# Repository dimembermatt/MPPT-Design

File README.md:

# :sunny: Sunscatter MPPT-Design - Gen 2 Maximum Power Point Tracker Board

Design and documentation of a custom MPPT for LHR Solar. Created in part with
Professor Alex Hanson's ECE 394J Power Electronics Class.

---

## Repository Structure

- **datasheets** - contains datasheets for major components of the Sunscatter.
- **docs** - contains documentation on how to build, test, and use the Sunscatter.
- **fw** - contains fw that is loaded onto the Sunscatter.
  - **tests** - test programs used to characterize and validate the Sunscatter.
  - **src** - main program used to run the Sunscatter.
  - **inc** - internally developed libraries specific for the Sunscatter.
  - **lib** - third party libraries used by the Sunscatter.
- **hw**
  - **footprints** - project specfic footprint association files for the Sunscatter.
  - **models** - 3d .step files for the PCB 3d viewer.
  - **symbols** - project specific symbol files for the Sunscatter.
  - **vX_Y_Z** - frozen versioning folder for PCB production files.
  - design files
- **sim** - contains a KiCAD project of the bare DC-DC converter of the MPPT, using SPICE parts for simulation.
- **sw** - contains relevant software for operating the automated design pipeline.
  - **design_files**
  - **design_procedures**

---

## Maintainers

The current maintainer of this project is Matthew Yu as of 07/17/2023. His email
is [matthewjkyu@gmail.com](matthewjkyu@gmail.com).

Contributors to the HW and FW encompass many dedicated students, including:

- Jacob Pustilnik
- Pranav Rama
- Sharon Chen

Special thanks to Professor Gary Hallock, who supervised the development and
design of this project.

---

## Versioning

This PCB is on unified version `0.2.0`. Every time the schematic and/or layout
is updated, this version number should go up. We use [semantic
versioning](https://semver.org/) to denote between versions. See the
[changelog](./docs/CHANGELOG.md) for more details.

---

## TODO

### Documentation

### HW

### FW

### SW

### Sim

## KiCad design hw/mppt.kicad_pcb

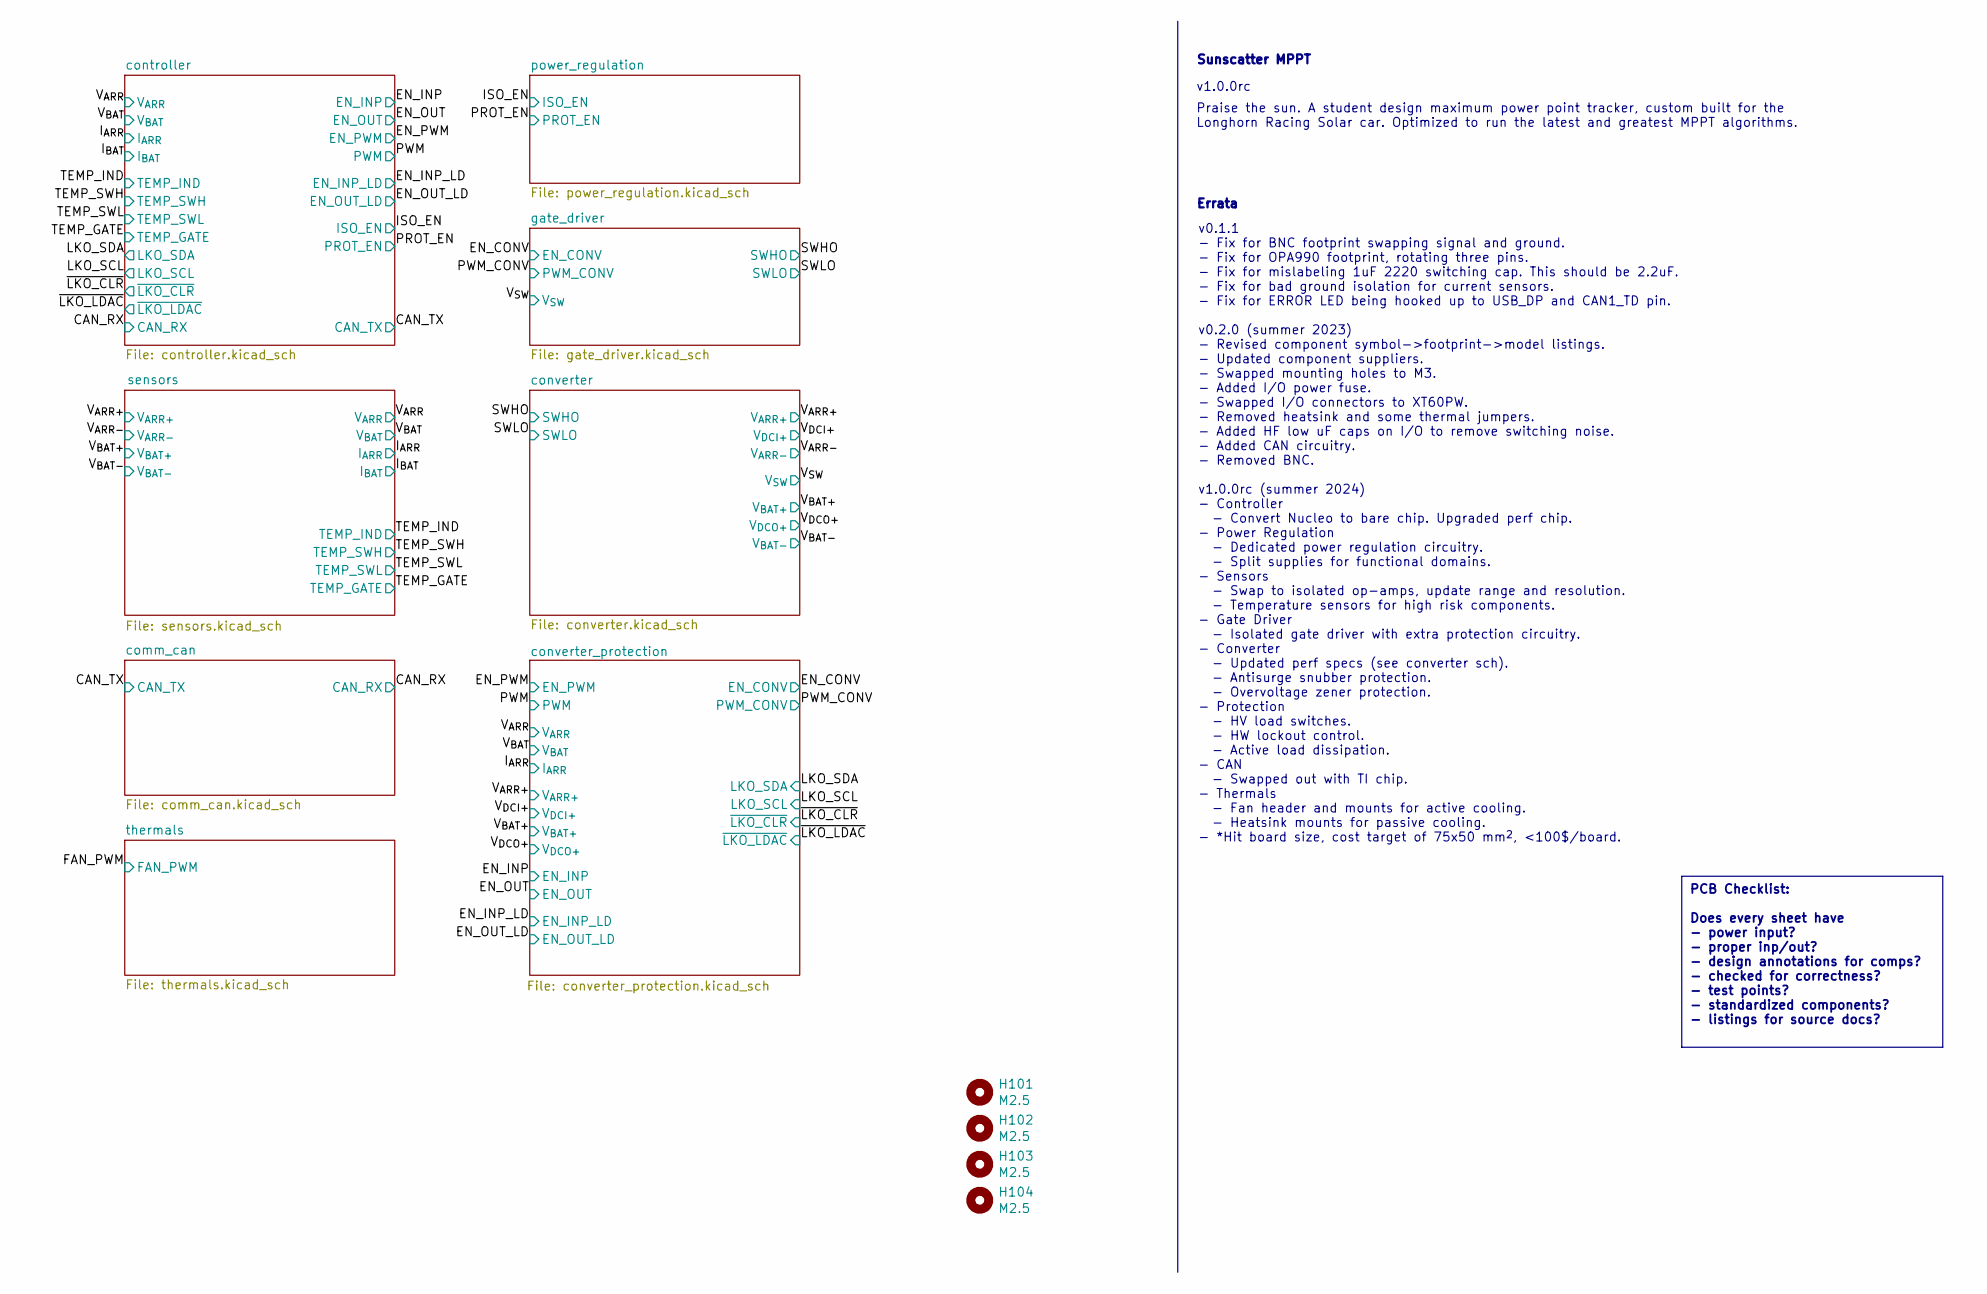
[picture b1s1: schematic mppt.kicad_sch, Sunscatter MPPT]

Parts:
H101, H102, H103, H104: M2.5; MountingHole_2.5mm

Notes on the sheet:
PCB Checklist: Does every sheet have - power input? - proper inp/out? - design annotations for comps? - checked for correctness? - test points? - standardized components? - listings for source docs?
Praise the sun. A student design maximum power point tracker, custom built for the Longhorn Racing Solar car. Optimized to run the latest and greatest MPPT algorithms.
Sunscatter MPPT
v1.0.0rc
Errata
v0.1.1 - Fix for BNC footprint swapping signal and ground. - Fix for OPA990 footprint, rotating three pins. - Fix for mislabeling 1uF 2220 switching cap. This should be 2.2uF. - Fix for bad ground isolation for current sensors. - Fix for ERROR LED being hooked up to USB_DP and CAN1_TD pin. v0.2.0 (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

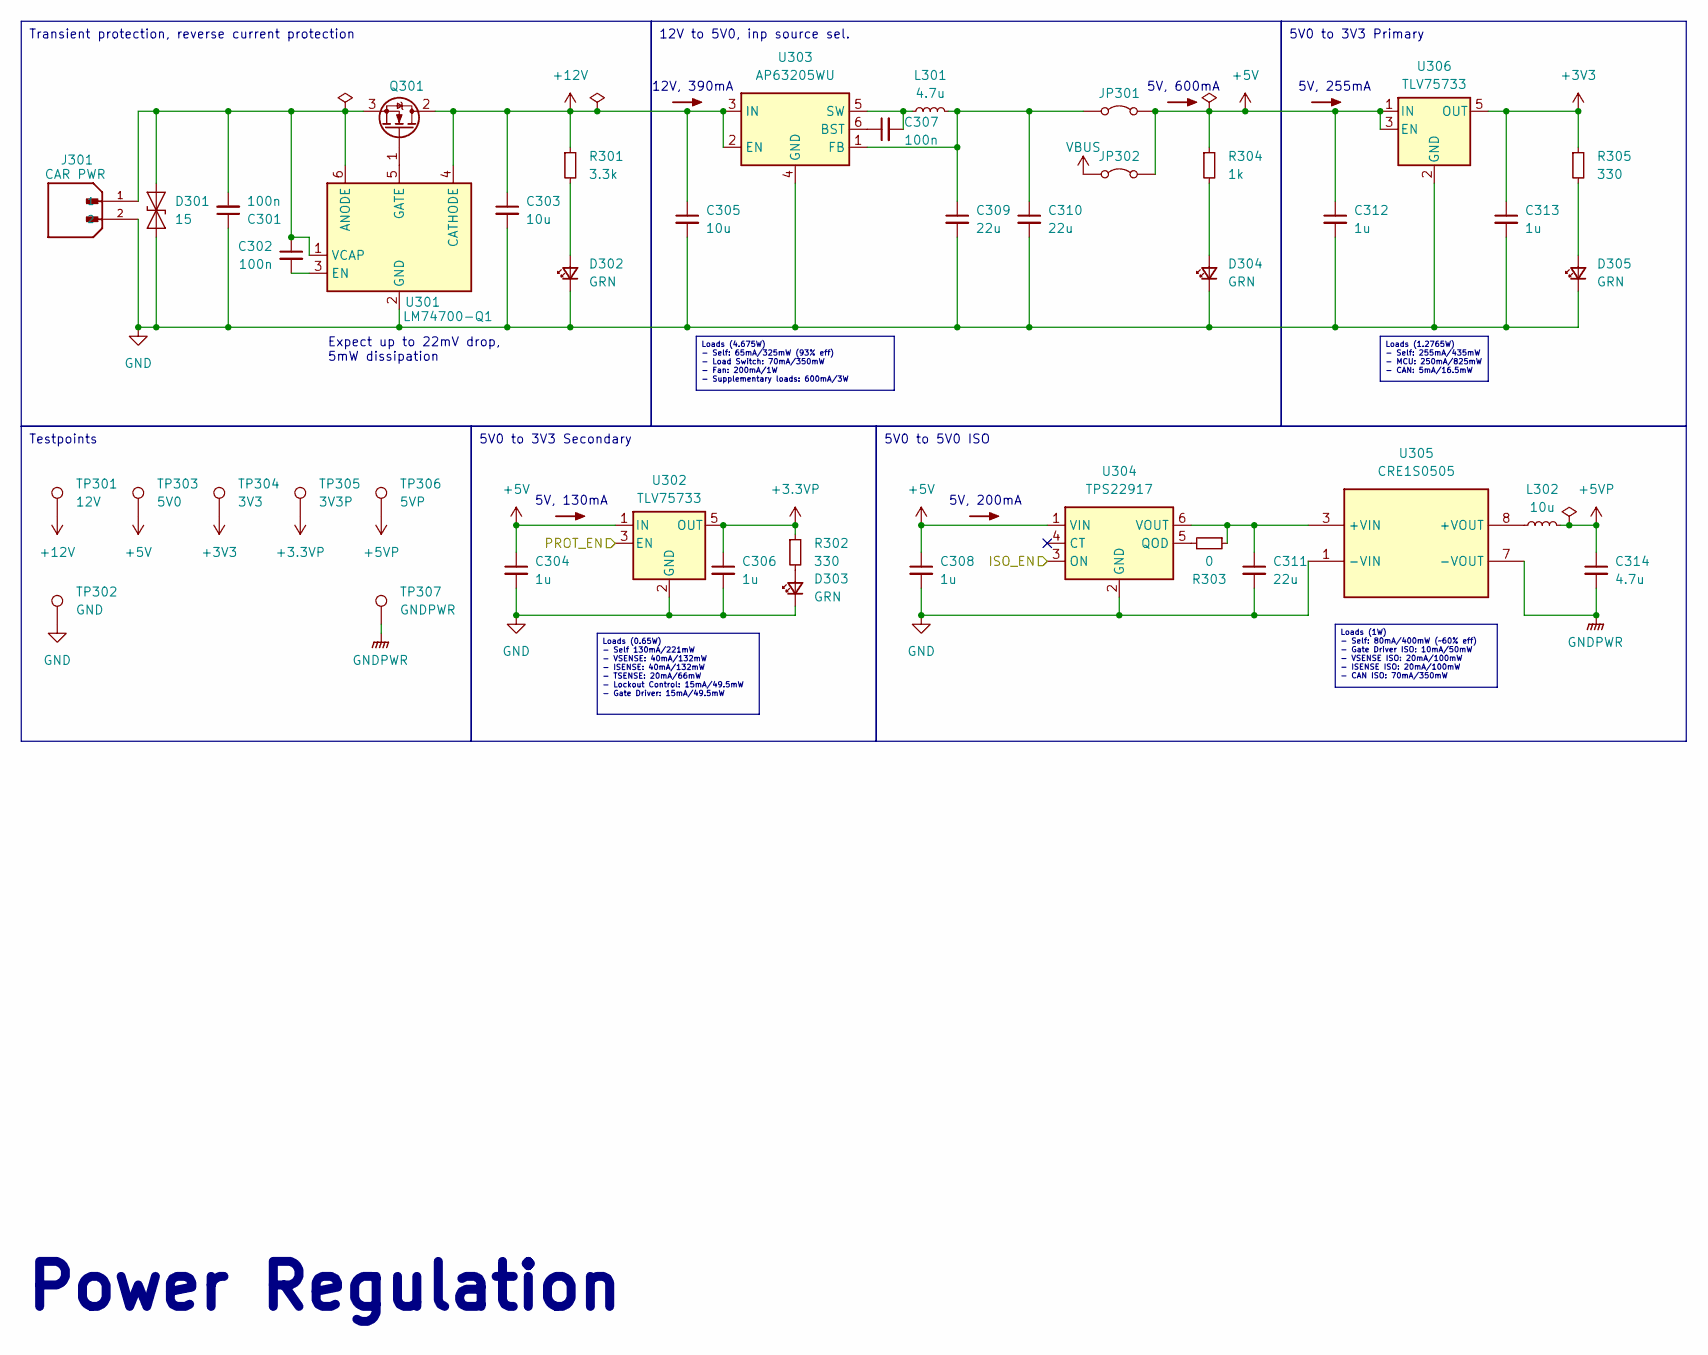
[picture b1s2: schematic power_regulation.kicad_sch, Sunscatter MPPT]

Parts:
C301, C302, C307: 100n; R_0402_1005Metric; LCSC Part # C307331
C303, C305: 10u; R_0805_2012Metric
C304, C306, C308, C312, C313: 1u; R_0402_1005Metric; LCSC Part # C307454
C309, C310, C311: 22u; R_0805_2012Metric
C314: 4.7u; R_0402_1005Metric; LCSC Part # C318563
D301: 15; D_SMA
D302, D303, D304, D305: GRN; LED_0402_1005Metric
J301: CAR PWR; molex_microfit_43650_0227
JP301, JP302: Jumper_2_Bridged; PinHeader_1x02_P2.54mm_Vertical
L301: 4.7u; L_TDK_VLS6045EX_VLS6045AF
L302: 10u; L_TDK_VLS6045EX_VLS6045AF
Q301: Q_NMOS_GDS; SOT-223-3_TabPin2
R301: 3.3k; R_0402_1005Metric; LCSC Part # C25890
R302, R305: 330; R_0402_1005Metric; LCSC Part # C25105
R303: 0; R_0402_1005Metric
R304: 1k; R_0402_1005Metric; LCSC Part # C11702
TP301: 12V; TestPoint_Pad_D1.5mm
TP302: GND; TestPoint_Pad_D1.5mm
TP303: 5V0; TestPoint_Pad_D1.5mm
TP304: 3V3; TestPoint_Pad_D1.5mm
TP305: 3V3P; TestPoint_Pad_D1.5mm
TP306: 5VP; TestPoint_Pad_D1.5mm
TP307: GNDPWR; TestPoint_Pad_D1.5mm
U301: LM74700-Q1; SOT-23-6
U302, U306: TLV75733; SOT-23-5
U303: AP63205WU; TSOT-23-6
U304: TPS22917; SOT-23-6
U305: CRE1S0505; murata_CRE1S0505_MEC

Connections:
+3.3VP: C306.1, R302.1, TP305.1, U302.5 (OUT); also elsewhere on the board
+3V3: C313.1, R305.1, TP304.1, U306.5 (OUT); also elsewhere on the board
+5V: C304.1, C308.1, C312.1, JP301.2 (B), JP302.2 (B), R304.1, TP303.1, U302.1 (IN), U304.1 (VIN), U306.1 (IN), U306.3 (EN); also elsewhere on the board
+5VP: C314.1, L302.2, TP306.1; also elsewhere on the board
+12V: C303.1, C305.1, Q301.2 (D), R301.1, TP301.1, U301.4 (CATHODE), U303.2 (EN), U303.3 (IN)
/ISO_EN: U304.3 (ON); also elsewhere on the board
/PROT_EN: U302.3 (EN); also elsewhere on the board
GND: C301.1, C303.2, C304.2, C305.2, C306.2, C308.2, C309.2, C310.2, C311.2, C312.2, C313.2, D301.1 (A1), D302.1 (K), D303.1 (K), D304.1 (K), D305.1 (K), J301.2, TP302.1, U301.2 (GND), U302.2 (GND), U303.4 (GND), U304.2 (GND), U305.1 (-VIN), U306.2 (GND); also elsewhere on the board
GNDPWR: C314.2, TP307.1, U305.7 (-VOUT); also elsewhere on the board
unnamed: C301.2, C302.1, D301.2 (A2), J301.1, Q301.3 (S), U301.1 (VCAP), U301.6 (ANODE)
unnamed: D302.2 (A), R301.2
unnamed: D303.2 (A), R302.2
unnamed: D304.2 (A), R304.2
unnamed: D305.2 (A), R305.2
unnamed: C309.1, C310.1, JP301.1 (A), L301.2, U303.1 (FB)
unnamed: Q301.1 (G), U301.5 (GATE)
unnamed: C302.2, U301.3 (EN)
unnamed: C307.1, U303.6 (BST)
unnamed: C307.2, L301.1, U303.5 (SW)
unnamed: R303.2, U304.5 (QOD)
unnamed: C311.1, R303.1, U304.6 (VOUT), U305.3 (+VIN)
unnamed: L302.1, U305.8 (+VOUT)
VBUS: JP302.1 (A); also elsewhere on the board

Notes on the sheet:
Testpoints
Loads (1W) - Self: 80mA/400mW (~60% eff) - Gate Driver ISO: 10mA/50mW - VSENSE ISO: 20mA/100mW - ISENSE ISO: 20mA/100mW - CAN ISO: 70mA/350mW
Transient protection, reverse current protection
5V0 to 3V3 Primary
5V0 to 5V0 ISO
Loads (4.675W) - Self: 65mA/325mW (93% eff) - Load Switch: 70mA/350mW - Fan: 200mA/1W - Supplementary loads: 600mA/3W
Loads (0.65W) - Self 130mA/221mW - VSENSE: 40mA/132mW - ISENSE: 40mA/132mW - TSENSE: 20mA/66mW - Lockout Control: 15mA/49.5mW - Gate Driver: 15mA/49.5mW
5V0 to 3V3 Secondary
12V to 5V0, inp source sel.
Loads (1.2765W) - Self: 255mA/435mW - MCU: 250mA/825mW - CAN: 5mA/16.5mW
Power Regulation
5V, 200mA
5V, 255mA
12V, 390mA
5V, 600mA
5V, 130mA
Expect up to 22mV drop, 5mW dissipation

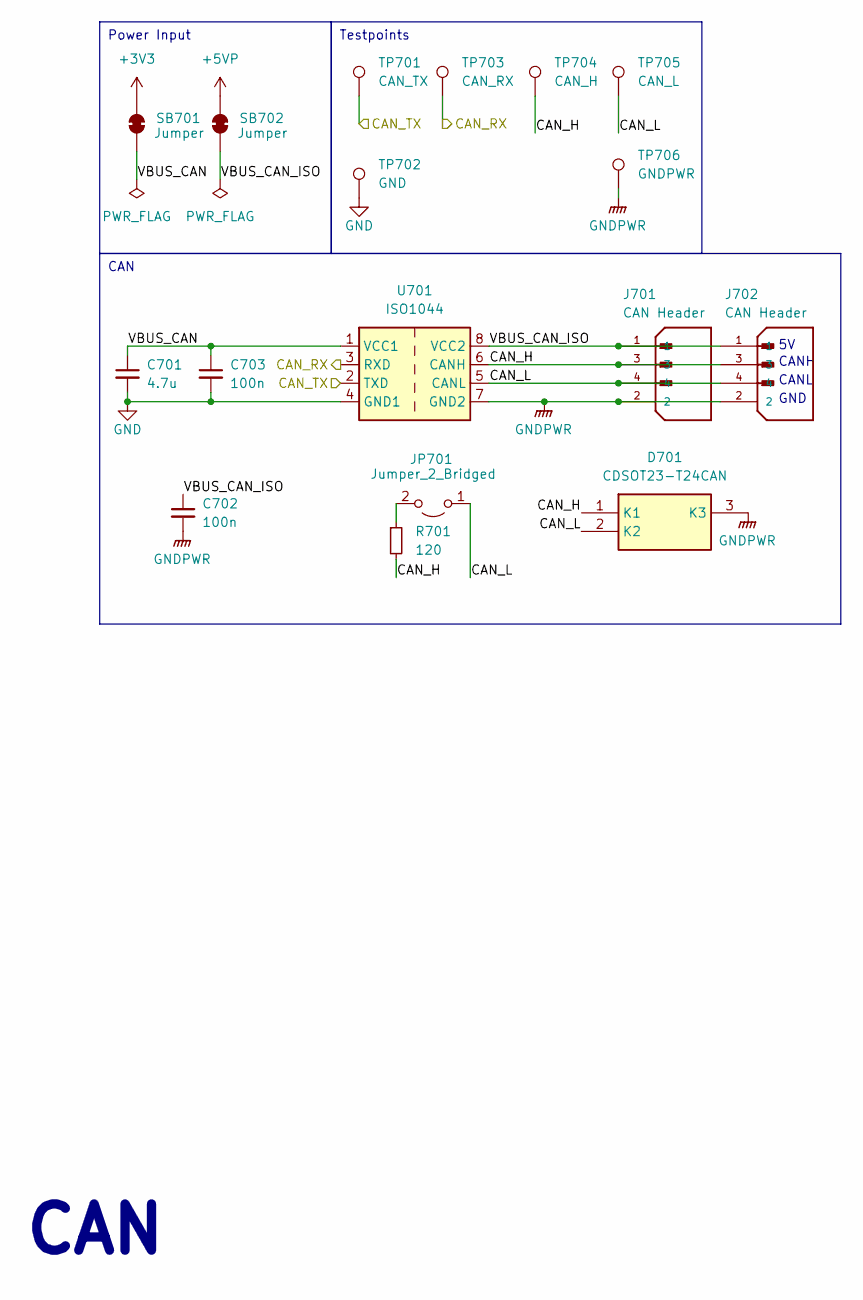
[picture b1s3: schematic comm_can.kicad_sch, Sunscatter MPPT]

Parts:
C701: 4.7u; R_0402_1005Metric; LCSC Part # C318563
C702, C703: 100n; R_0402_1005Metric; LCSC Part # C307331
D701: CDSOT23-T24CAN; bourns_CDSOT23_T24CAN
J701, J702: CAN Header; molex_microfit_43650_0427
JP701: Jumper_2_Bridged; PinHeader_1x02_P2.54mm_Vertical
R701: 120; R_0402_1005Metric; LCSC Part # C25079
SB701, SB702: Jumper; SolderJumper-2_P1.3mm_Open_TrianglePad1.0x1.5mm
TP701: CAN_TX; TestPoint_Pad_D1.5mm
TP702: GND; TestPoint_Pad_D1.5mm
TP703: CAN_RX; TestPoint_Pad_D1.5mm
TP704: CAN_H; TestPoint_Pad_D1.5mm
TP705: CAN_L; TestPoint_Pad_D1.5mm
TP706: GNDPWR; TestPoint_Pad_D1.5mm
U701: ISO1044; SOIC-8_3.9x4.9mm_P1.27mm

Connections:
+3V3: SB701.1 (A); also elsewhere on the board
+5VP: SB702.1 (A); also elsewhere on the board
/CAN_RX: TP703.1, U701.3 (RXD); also elsewhere on the board
/CAN_TX: TP701.1, U701.2 (TXD); also elsewhere on the board
/comm_can/CAN_H: D701.1 (K1), J701.3, J702.3, R701.2, TP704.1, U701.6 (CANH)
/comm_can/CAN_L: D701.2 (K2), J701.4, J702.4, JP701.1 (A), TP705.1, U701.5 (CANL)
/comm_can/VBUS_CAN: C701.1, C703.1, SB701.2 (B), U701.1 (VCC1)
/comm_can/VBUS_CAN_ISO: C702.1, J701.1, J702.1, SB702.2 (B), U701.8 (VCC2)
GND: C701.2, C703.2, TP702.1, U701.4 (GND1); also elsewhere on the board
GNDPWR: C702.2, D701.3 (K3), J701.2, J702.2, TP706.1, U701.7 (GND2); also elsewhere on the board
unnamed: JP701.2 (B), R701.1

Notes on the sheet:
CAN
Power Input
Testpoints
CANH
GND
CANL

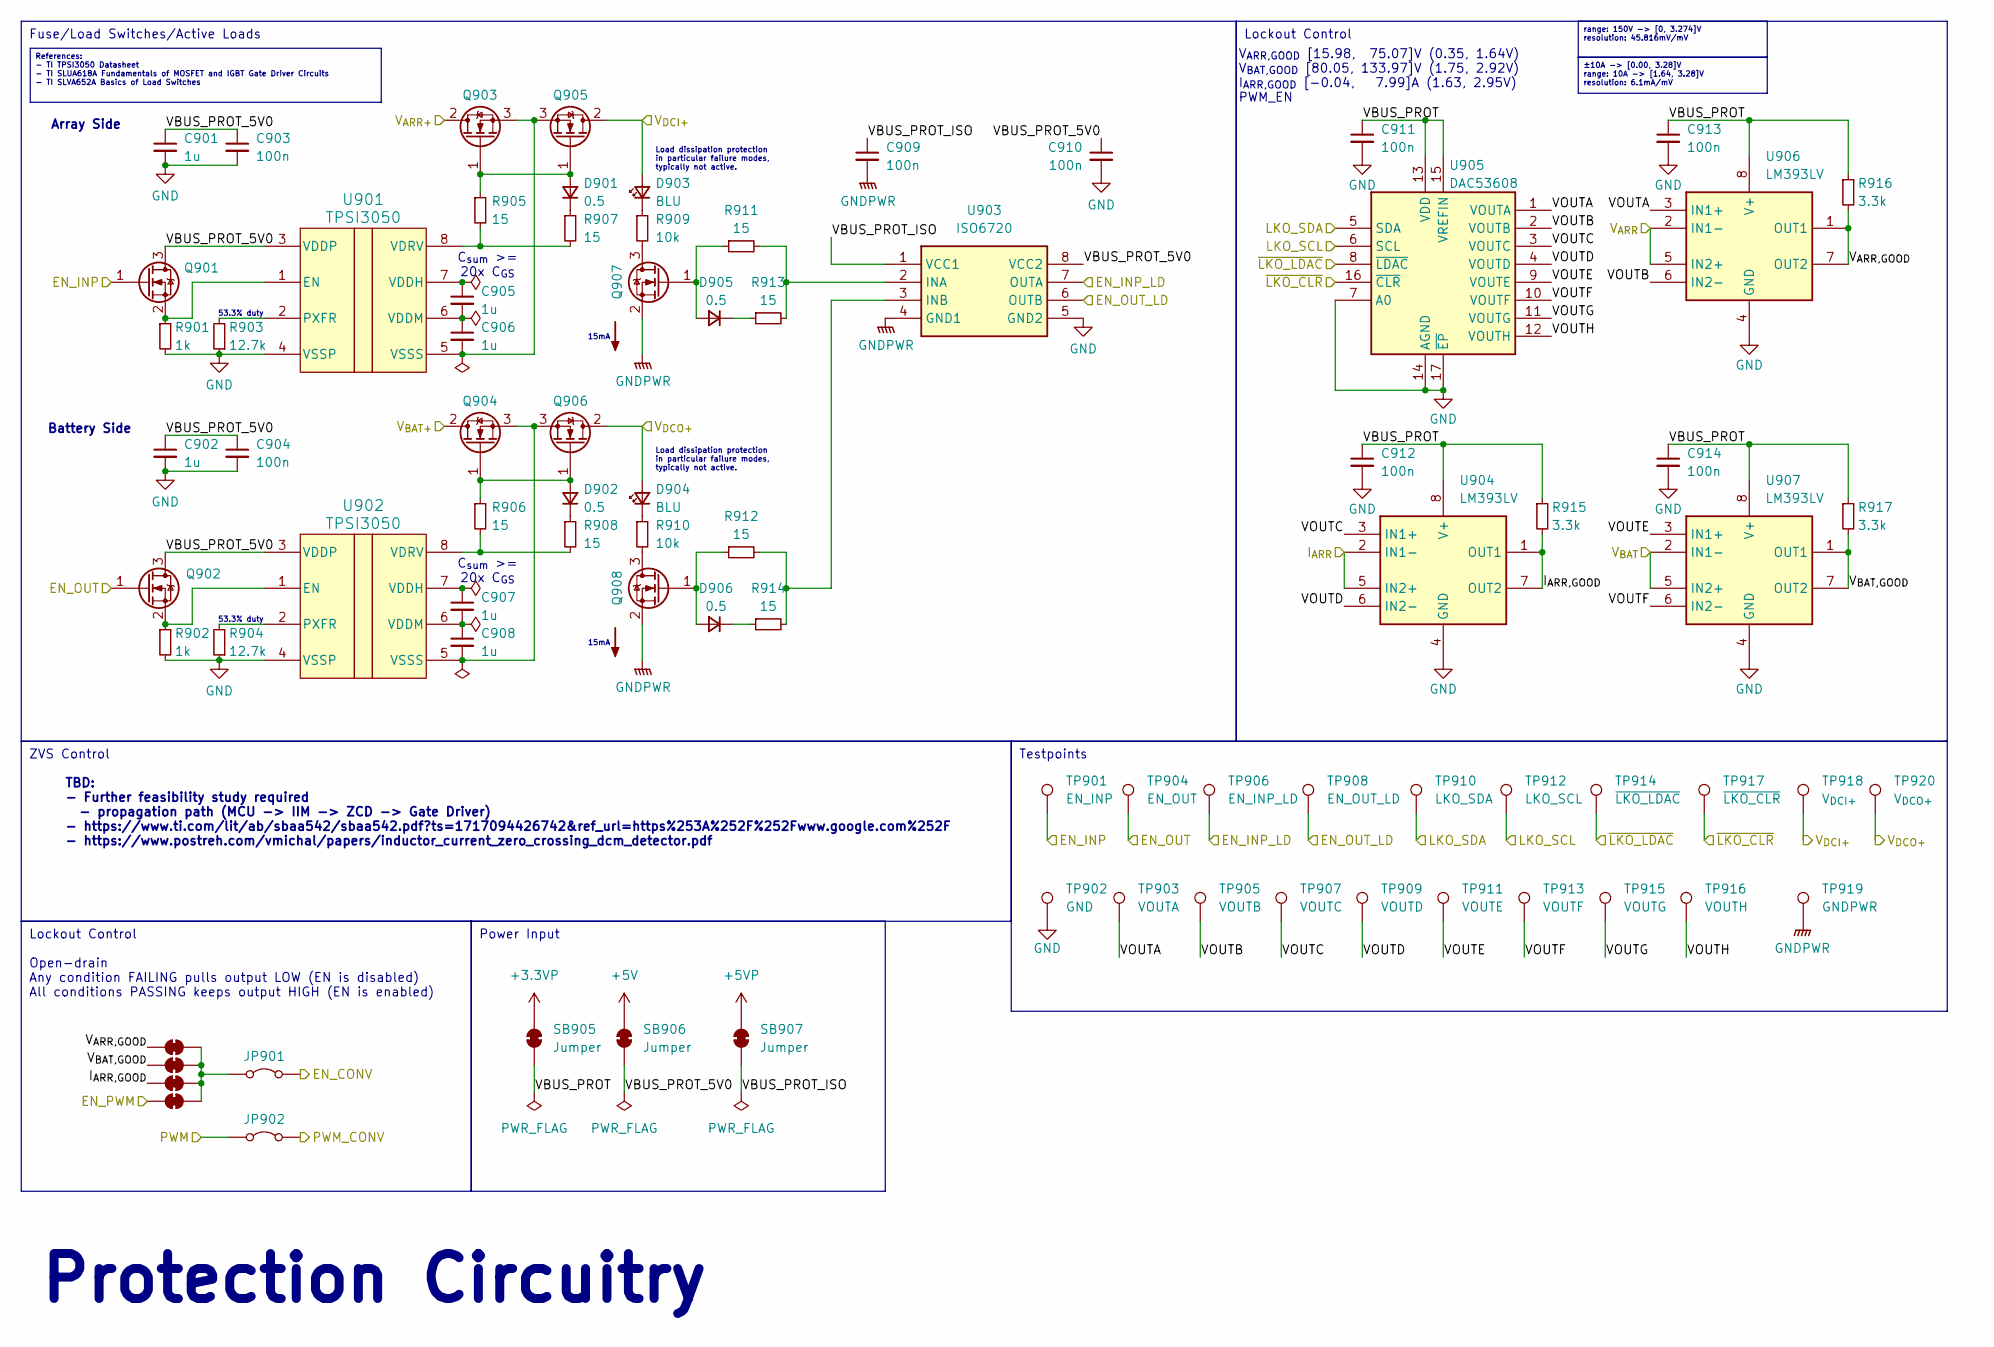
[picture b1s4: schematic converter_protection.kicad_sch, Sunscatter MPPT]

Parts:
C901, C902, C905, C906, C907, C908: 1u; R_0402_1005Metric; LCSC Part # C307454
C903, C904, C909, C910, C911, C912, C913, C914: 100n; R_0402_1005Metric; LCSC Part # C307331
D901, D902, D905, D906: 0.5; D_SMA
D903, D904: BLU; LED_0402_1005Metric
JP901, JP902: Jumper_2_Bridged; PinHeader_1x02_P2.54mm_Vertical
Q901, Q902, Q907, Q908: BSS127S; SOT-23
Q903, Q904, Q905, Q906: Q_NMOS_GDS; SOT-223-3_TabPin2
R901, R902: 1k; R_0402_1005Metric; LCSC Part # C11702
R903, R904: 12.7k; R_0402_1005Metric; LCSC Part # C25853
R905, R906, R907, R908, R911, R912, R913, R914: 15; R_0603_1608Metric; LCSC Part # C22810
R909, R910: 10k; R_2512_6332Metric_Pad1.40x3.35mm_HandSolder
R915, R916, R917: 3.3k; R_0402_1005Metric; LCSC Part # C25890
SB901, SB902, SB903, SB904, SB905, SB906, SB907: Jumper; SolderJumper-2_P1.3mm_Open_TrianglePad1.0x1.5mm
TP901: EN_INP; TestPoint_Pad_D1.5mm
TP902: GND; TestPoint_Pad_D1.5mm
TP903: VOUTA; TestPoint_Pad_D1.5mm
TP904: EN_OUT; TestPoint_Pad_D1.5mm
TP905: VOUTB; TestPoint_Pad_D1.5mm
TP906: EN_INP_LD; TestPoint_Pad_D1.5mm
TP907: VOUTC; TestPoint_Pad_D1.5mm
TP908: EN_OUT_LD; TestPoint_Pad_D1.5mm
TP909: VOUTD; TestPoint_Pad_D1.5mm
TP910: LKO_SDA; TestPoint_Pad_D1.5mm
TP911: VOUTE; TestPoint_Pad_D1.5mm
TP912: LKO_SCL; TestPoint_Pad_D1.5mm
TP913: VOUTF; TestPoint_Pad_D1.5mm
TP914: ~{LKO_LDAC}; TestPoint_Pad_D1.5mm
TP915: VOUTG; TestPoint_Pad_D1.5mm
TP916: VOUTH; TestPoint_Pad_D1.5mm
TP917: ~{LKO_CLR}; TestPoint_Pad_D1.5mm
TP918: V_{DCI+}; TestPoint_Pad_D1.5mm
TP919: GNDPWR; TestPoint_Pad_D1.5mm
TP920: V_{DCO+}; TestPoint_Pad_D1.5mm
U901, U902: TPSI3050; ti_TPS3050_DWZ
U903: ISO6720; ti_ISO6720B_DR
U904, U906, U907: LM393LV; ti_LM393LV_DR
U905: DAC53608; ti_DAC53608_RT

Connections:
+3.3VP: SB905.2 (B); also elsewhere on the board
+5V: SB906.2 (B); also elsewhere on the board
+5VP: SB907.2 (B); also elsewhere on the board
/EN_CONV: JP901.2 (B); also elsewhere on the board
/EN_INP: Q901.1 (G), TP901.1; also elsewhere on the board
/EN_INP_LD: TP906.1, U903.7 (OUTA); also elsewhere on the board
/EN_OUT: Q902.1 (G), TP904.1; also elsewhere on the board
/EN_OUT_LD: TP908.1, U903.6 (OUTB); also elsewhere on the board
/EN_PWM: SB904.1 (A); also elsewhere on the board
/I_{ARR}: U904.2 (IN1-), U904.5 (IN2+); also elsewhere on the board
/LKO_SCL: TP912.1, U905.6 (SCL); also elsewhere on the board
/LKO_SDA: TP910.1, U905.5 (SDA); also elsewhere on the board
/PWM: JP902.1 (A); also elsewhere on the board
/PWM_CONV: JP902.2 (B); also elsewhere on the board
/V_{ARR+}: Q903.2 (D); also elsewhere on the board
/V_{ARR}: U906.2 (IN1-), U906.5 (IN2+); also elsewhere on the board
/V_{BAT+}: Q904.2 (D); also elsewhere on the board
/V_{BAT}: U907.2 (IN1-), U907.5 (IN2+); also elsewhere on the board
/V_{DCI+}: D903.2 (A), Q905.2 (D), TP918.1; also elsewhere on the board
/V_{DCO+}: D904.2 (A), Q906.2 (D), TP920.1; also elsewhere on the board
/converter_protection/I_{ARR,GOOD}: R915.2, SB903.1 (A), U904.1 (OUT1), U904.7 (OUT2)
/converter_protection/VBUS_PROT: C911.1, C912.1, C913.1, C914.1, R915.1, R916.1, R917.1, SB905.1 (A), U904.8 (V+), U905.13 (VDD), U905.15 (VREFIN), U906.8 (V+), U907.8 (V+)
/converter_protection/VBUS_PROT_5V0: C901.1, C902.1, C903.1, C904.1, C910.1, Q901.3 (D), Q902.3 (D), SB906.1 (A), U901.3 (VDDP), U902.3 (VDDP), U903.8 (VCC2)
/converter_protection/VBUS_PROT_ISO: C909.1, SB907.1 (A), U903.1 (VCC1)
/converter_protection/VOUTA: TP903.1, U905.1 (VOUTA), U906.3 (IN1+)
/converter_protection/VOUTB: TP905.1, U905.2 (VOUTB), U906.6 (IN2-)
/converter_protection/VOUTC: TP907.1, U904.3 (IN1+), U905.3 (VOUTC)
/converter_protection/VOUTD: TP909.1, U904.6 (IN2-), U905.4 (VOUTD)
/converter_protection/VOUTE: TP911.1, U905.9 (VOUTE), U907.3 (IN1+)
/converter_protection/VOUTF: TP913.1, U905.10 (VOUTF), U907.6 (IN2-)
/converter_protection/VOUTG: TP915.1, U905.11 (VOUTG)
/converter_protection/VOUTH: TP916.1, U905.12 (VOUTH)
/converter_protection/V_{ARR,GOOD}: R916.2, SB901.1 (A), U906.1 (OUT1), U906.7 (OUT2)
/converter_protection/V_{BAT,GOOD}: R917.2, SB902.1 (A), U907.1 (OUT1), U907.7 (OUT2)
/~LKO_CLR: TP917.1, U905.16 (~CLR); also elsewhere on the board
/~LKO_LDAC: TP914.1, U905.8 (~LDAC); also elsewhere on the board
GND: C901.2, C902.2, C903.2, C904.2, C910.2, C911.2, C912.2, C913.2, C914.2, R901.2, R902.2, R903.1, R904.1, TP902.1, U901.4 (VSSP), U902.4 (VSSP), U903.5 (GND2), U904.4 (GND), U905.7 (A0), U905.14 (AGND), U905.17 (~EP), U906.4 (GND), U907.4 (GND); also elsewhere on the board
GNDPWR: C909.2, Q907.2 (S), Q908.2 (S), TP919.1, U903.4 (GND1); also elsewhere on the board
unnamed: D901.2 (A), Q903.1 (G), Q905.1 (G), R905.1
unnamed: D901.1 (K), R907.1
unnamed: D902.2 (A), Q904.1 (G), Q906.1 (G), R906.1
unnamed: D902.1 (K), R908.1
unnamed: D903.1 (K), R909.1
unnamed: D904.1 (K), R910.1
unnamed: D905.2 (A), Q907.1 (G), R911.1
unnamed: D905.1 (K), R913.1
unnamed: D906.2 (A), Q908.1 (G), R912.1
unnamed: D906.1 (K), R914.1
unnamed: JP901.1 (A), SB901.2 (B), SB902.2 (B), SB903.2 (B), SB904.2 (B)
unnamed: Q901.2 (S), R901.1, U901.1 (EN)
unnamed: Q902.2 (S), R902.1, U902.1 (EN)
unnamed: C906.2, Q903.3 (S), Q905.3 (S), U901.5 (VSSS)
unnamed: C908.2, Q904.3 (S), Q906.3 (S), U902.5 (VSSS)
unnamed: Q907.3 (D), R909.2
unnamed: Q908.3 (D), R910.2
unnamed: R903.2, U901.2 (PXFR)
unnamed: C905.1, U901.7 (VDDH)
unnamed: C905.2, C906.1, U901.6 (VDDM)
unnamed: R905.2, R907.2, U901.8 (VDRV)
unnamed: R904.2, U902.2 (PXFR)
unnamed: C907.1, U902.7 (VDDH)
unnamed: C907.2, C908.1, U902.6 (VDDM)
unnamed: R906.2, R908.2, U902.8 (VDRV)
unnamed: R911.2, R913.2, U903.2 (INA)
unnamed: R912.2, R914.2, U903.3 (INB)

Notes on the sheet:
Testpoints
range: 150V -> [0, 3.274]V resolution: 45.816mV/mV
Lockout Control Open-drain Any condition FAILING pulls output LOW (EN is disabled) All conditions PASSING keeps output HIGH (EN is enabled)
ZVS Control
±10A -> [0.00, 3.28]V range: 10A -> [1.64, 3.28]V resolution: 6.1mA/mV
Fuse/Load Switches/Active Loads
References: - TI TPSI3050 Datasheet - TI SLUA618A Fundamentals of MOSFET and IGBT Gate Driver Circuits - TI SLVA652A Basics of Load Switches
Power Input
Lockout Control
Array Side
C_{sum} >= 20x C_{GS}
Protection Circuitry
Load dissipation protection in particular failure modes, typically not active.
TBD: - Further feasibility study required - propagation path (MCU -> IIM -> ZCD -> Gate Driver) - https://www.ti.com/lit/ab/sbaa542/sbaa542.pdf?ts=1717094426742&ref_url=https%253A%252F%252Fwww.google.com%252F - https://www.postreh.com/vmichal/papers/inductor_current_zero_crossing_dcm_detector.pdf
Battery Side
53.3% duty
15mA
V_{ARR,GOOD} [15.98, 75.07]V (0.35, 1.64V) V_{BAT,GOOD} [80.05, 133.97]V (1.75, 2.92V) I_{ARR,GOOD} [-0.04, 7.99]A (1.63, 2.95V) PWM_EN

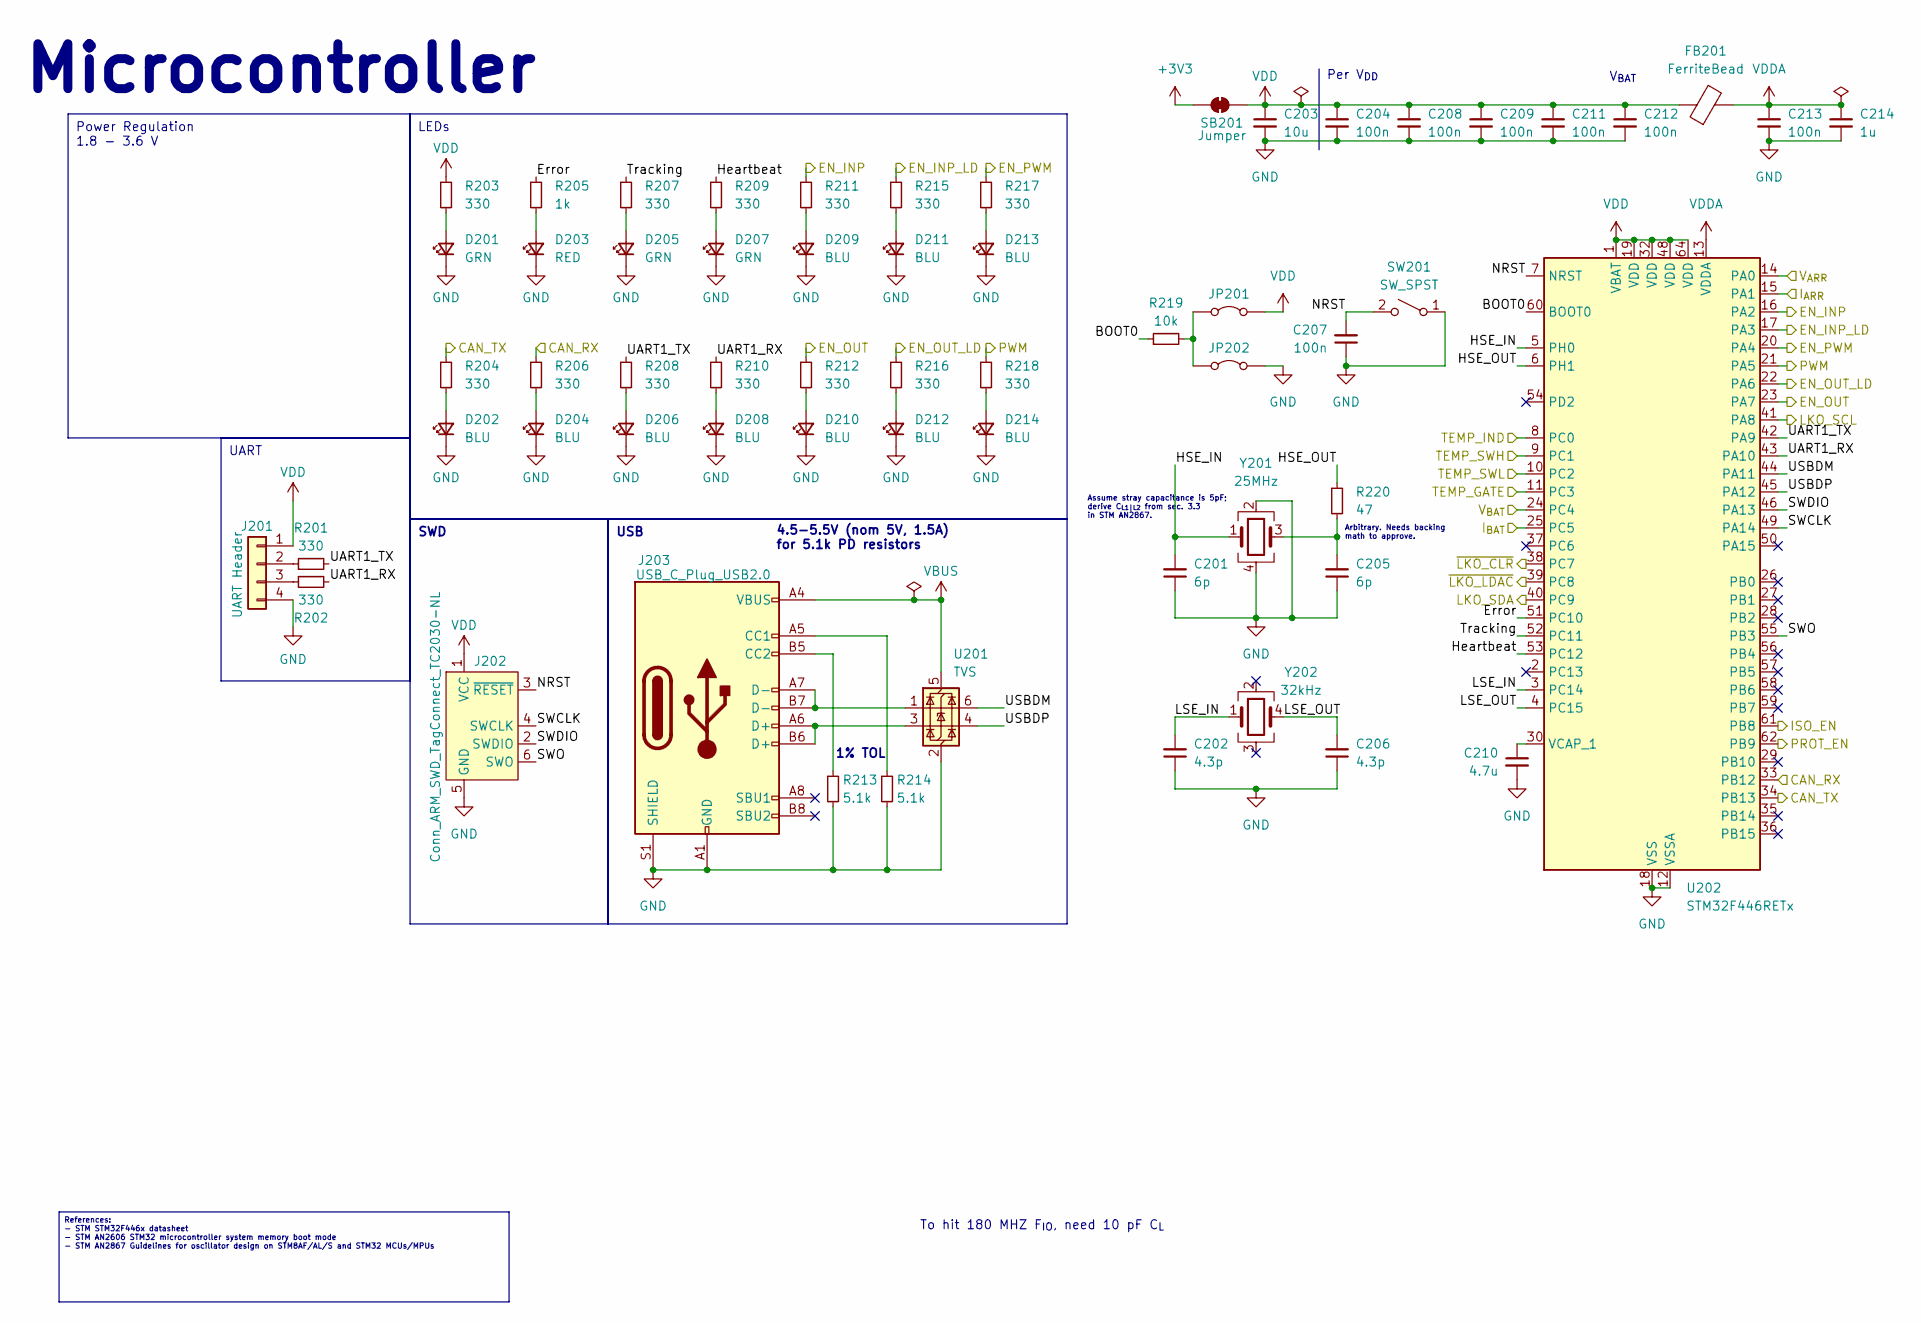
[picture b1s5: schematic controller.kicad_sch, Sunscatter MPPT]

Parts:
C201, C205: 6p; R_0402_1005Metric; LCSC Part # C318621
C202, C206: 4.3p; R_0402_1005Metric; LCSC Part # C159803
C203: 10u; R_0805_2012Metric
C204, C207, C208, C209, C211, C212, C213: 100n; R_0402_1005Metric; LCSC Part # C307331
C210: 4.7u; R_0402_1005Metric; LCSC Part # C318563
C214: 1u; R_0402_1005Metric; LCSC Part # C307454
D201, D205, D207: GRN; LED_0402_1005Metric
D202, D204, D206, D208, D209, D210, D211, D212, D213, D214: BLU; LED_0402_1005Metric
D203: RED; LED_0402_1005Metric
FB201: FerriteBead; R_0402_1005Metric
J201: UART Header; molex_microfit_43650_0427
J202: Conn_ARM_SWD_TagConnect_TC2030-NL; Tag-Connect_TC2030-IDC-NL_2x03_P1.27mm_Vertical
J203: USB_C_Plug_USB2.0; USB_C_Receptacle_GCT_USB4105-xx-A_16P_TopMnt_Horizontal
JP201, JP202: Jumper_2_Bridged; PinHeader_1x02_P2.54mm_Vertical
R201, R202, R203, R204, R206, R207, R208, R209, R210, R211, R212, R215, R216, R217, R218: 330; R_0402_1005Metric; LCSC Part # C25105
R205: 1k; R_0402_1005Metric; LCSC Part # C11702
R213, R214: 5.1k; R_0402_1005Metric; LCSC Part # C25905
R219: 10k; R_0402_1005Metric; LCSC Part # C25744
R220: 47; R_0402_1005Metric; LCSC Part # C25118
SB201: Jumper; SolderJumper-2_P1.3mm_Open_TrianglePad1.0x1.5mm
SW201: SW_SPST; SW_Push_1P1T_XKB_TS-1187A; LCSC Part # C318884
U201: TVS; SOT-23-6
U202: STM32F446RETx; LQFP-64_10x10mm_P0.5mm
Y201: 25MHz; Crystal_SMD_Abracon_ABM8AIG-4Pin_3.2x2.5mm
Y202: 32kHz; Crystal_SMD_Abracon_ABS25-4Pin_8.0x3.8mm; LCSC Part # C1985642

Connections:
+3V3: SB201.2 (B); also elsewhere on the board
/CAN_RX: R206.1, U202.33 (PB12); also elsewhere on the board
/CAN_TX: R204.1, U202.34 (PB13); also elsewhere on the board
/EN_INP: R211.1, U202.16 (PA2); also elsewhere on the board
/EN_INP_LD: R215.1, U202.17 (PA3); also elsewhere on the board
/EN_OUT: R212.1, U202.23 (PA7); also elsewhere on the board
/EN_OUT_LD: R216.1, U202.22 (PA6); also elsewhere on the board
/EN_PWM: R217.1, U202.20 (PA4); also elsewhere on the board
/ISO_EN: U202.61 (PB8); also elsewhere on the board
/I_{ARR}: U202.15 (PA1); also elsewhere on the board
/I_{BAT}: U202.25 (PC5); also elsewhere on the board
/LKO_SCL: U202.41 (PA8); also elsewhere on the board
/LKO_SDA: U202.40 (PC9); also elsewhere on the board
/PROT_EN: U202.62 (PB9); also elsewhere on the board
/PWM: R218.1, U202.21 (PA5); also elsewhere on the board
/TEMP_GATE: U202.11 (PC3); also elsewhere on the board
/TEMP_IND: U202.8 (PC0); also elsewhere on the board
/TEMP_SWH: U202.9 (PC1); also elsewhere on the board
/TEMP_SWL: U202.10 (PC2); also elsewhere on the board
/V_{ARR}: U202.14 (PA0); also elsewhere on the board
/V_{BAT}: U202.24 (PC4); also elsewhere on the board
/controller/BOOT0: R219.1, U202.60 (BOOT0)
/controller/Error: R205.1, U202.51 (PC10)
/controller/HSE_IN: C201.2, U202.5 (PH0), Y201.1
/controller/HSE_OUT: R220.1, U202.6 (PH1)
/controller/Heartbeat: R209.1, U202.53 (PC12)
/controller/LSE_IN: C202.2, U202.3 (PC14), Y202.1
/controller/LSE_OUT: C206.2, U202.4 (PC15), Y202.4
/controller/NRST: C207.2, J202.3 (~RESET), SW201.2 (B), U202.7 (NRST)
/controller/SWCLK: J202.4 (SWCLK), U202.49 (PA14)
/controller/SWDIO: J202.2 (SWDIO), U202.46 (PA13)
/controller/SWO: J202.6 (SWO), U202.55 (PB3)
/controller/Tracking: R207.1, U202.52 (PC11)
/controller/UART1_RX: R202.2, R210.1, U202.43 (PA10)
/controller/UART1_TX: R201.2, R208.1, U202.42 (PA9)
/controller/USBDM: U201.6 (I/O1), U202.44 (PA11)
/controller/USBDP: U201.4 (I/O2), U202.45 (PA12)
/~LKO_CLR: U202.38 (PC7); also elsewhere on the board
/~LKO_LDAC: U202.39 (PC8); also elsewhere on the board
GND: C201.1, C202.1, C203.2, C204.2, C205.1, C206.1, C207.1, C208.2, C209.2, C210.2, C211.2, C212.2, C213.2, C214.2, D201.1 (K), D202.1 (K), D203.1 (K), D204.1 (K), D205.1 (K), D206.1 (K), D207.1 (K), D208.1 (K), D209.1 (K), D210.1 (K), D211.1 (K), D212.1 (K), D213.1 (K), D214.1 (K), J201.4, J202.5 (GND), J203.A1 (GND), J203.A12 (GND), J203.B1 (GND), J203.B12 (GND), J203.S1 (SHIELD), JP202.2 (B), R213.2, R214.2, SW201.1 (A), U201.2 (GND), U202.12 (VSSA), U202.18 (VSS), U202.31 (VSS), U202.47 (VSS), U202.63 (VSS), Y201.2, Y201.4; also elsewhere on the board
unnamed: C205.2, R220.2, Y201.3
unnamed: D201.2 (A), R203.2
unnamed: D202.2 (A), R204.2
unnamed: D203.2 (A), R205.2
unnamed: D204.2 (A), R206.2
unnamed: D205.2 (A), R207.2
unnamed: D206.2 (A), R208.2
unnamed: D207.2 (A), R209.2
unnamed: D208.2 (A), R210.2
unnamed: D209.2 (A), R211.2
unnamed: D210.2 (A), R212.2
unnamed: D211.2 (A), R215.2
unnamed: D212.2 (A), R216.2
unnamed: D213.2 (A), R217.2
unnamed: D214.2 (A), R218.2
unnamed: J201.2, R201.1
unnamed: J201.3, R202.1
unnamed: J203.A5 (CC1), R214.1
unnamed: J203.B5 (CC2), R213.1
unnamed: J203.A6 (D+), J203.B6 (D+), U201.3 (I/O2)
unnamed: J203.A7 (D-), J203.B7 (D-), U201.1 (I/O1)
unnamed: JP201.1 (A), JP202.1 (A), R219.2
unnamed: C210.1, U202.30 (VCAP_1)
VBUS: J203.A4 (VBUS), J203.A9 (VBUS), J203.B4 (VBUS), J203.B9 (VBUS), U201.5 (VBUS); also elsewhere on the board
VDD: C203.1, C204.1, C208.1, C209.1, C211.1, C212.1, FB201.1, J201.1, J202.1 (VCC), JP201.2 (B), R203.1, SB201.1 (A), U202.1 (VBAT), U202.19 (VDD), U202.32 (VDD), U202.48 (VDD), U202.64 (VDD)
VDDA: C213.1, C214.1, FB201.2, U202.13 (VDDA)

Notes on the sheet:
USB
References: - STM STM32F446x datasheet - STM AN2606 STM32 microcontroller system memory boot mode - STM AN2867 Guidelines for oscillator design on STM8AF/AL/S and STM32 MCUs/MPUs
Power Regulation 1.8 - 3.6 V
UART
SWD
LEDs
Microcontroller
4.5-5.5V (nom 5V, 1.5A) for 5.1k PD resistors
Arbitrary. Needs backing math to approve.
1% TOL
V_{BAT}
To hit 180 MHZ F_{IO}, need 10 pF C_{L}
Per V_{DD}
Assume stray capacitance is 5pF; derive C_{L1|L2} from sec. 3.3 in STM AN2867.
